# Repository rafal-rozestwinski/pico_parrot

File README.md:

# pico_parrot

Baofeng Parrot Simplex Repeater by Rafał Rozestwiński, https://github.com/rafal-rozestwinski/pico_parrot

- Listens for transmission,
- If audio level is high, it records audio for 10s,
- After 10s, triggers PTT on baofeng,
- plays beep (from sample.h),
- plays recorded audio,
- plays beep, releases PTT.

Based on https://github.com/rgrosset/pico-pwm-audio

Refer to it on how to generate own sample.h header with a custom beep (you may want to put your callsign there).

## Board

## Schematic

[schematic.pdf](/schematic.pdf)

## BoM

Footprints are duplicated - either SMT or THT parts can be used.
All part values are written on the PCB itself.

- 1x Raspberry Pi Pico
- 1x BJT transistor 2n3904
- 2x PCB Audio Jack Socket PJ-307
- 2x 100nF capacitor
- 1x bigger capacitor (10uF+)
- Resitors:
  - 2x 1000R pot, tht, RM-065_Vertical
  - 220
  - 100
  - 2x 1.8k
  - 2x 68k (or 56k... or 92k etc.) 

Optional power supply regulator pads are for AMS1117-5.0V.

## Future Plans

- Detect end of transmission and play back sooner.
- Easy way to change beep: littlefs has been added, need to add USB Mass Storage support, so those can be replaced without recompiling the code.
- Remote control over USB?
- 3D printed case

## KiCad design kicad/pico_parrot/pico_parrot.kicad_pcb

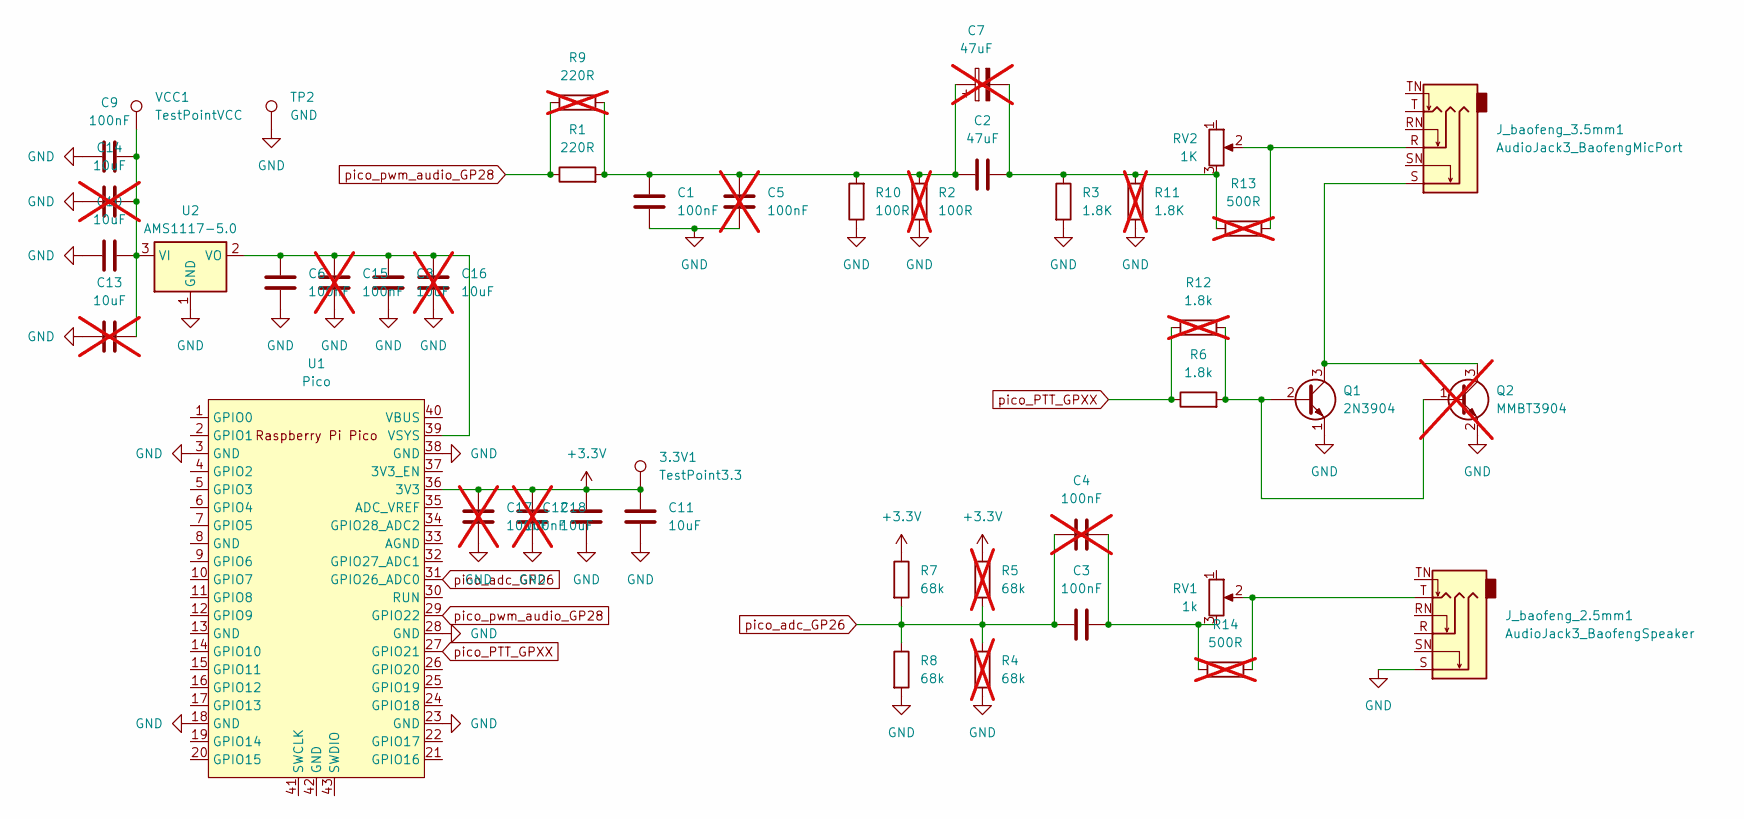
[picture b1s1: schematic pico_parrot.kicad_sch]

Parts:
3.3V1: TestPoint3.3; TestPoint_Pad_2.0x2.0mm
C1, C3, C6, C9, C12: 100nF; C_1206_3216Metric
C2: 47uF; C_1206_3216Metric
C4, C5, C15, C17: 100nF; C_Disc_D4.3mm_W1.9mm_P5.00mm; not fitted
C7: 47uF; CP_Radial_D5.0mm_P2.50mm; not fitted
C8, C10, C11: 10uF; C_1206_3216Metric
C13, C14, C16, C18: 10uF; C_Disc_D4.3mm_W1.9mm_P5.00mm; not fitted
J_baofeng_2.5mm1: AudioJack3_BaofengSpeaker; PJ-307_Modded
J_baofeng_3.5mm1: AudioJack3_BaofengMicPort; PJ-307_Modded
Q1: 2N3904; TO-92_Inline
Q2: MMBT3904; SOT-23; not fitted
R1: 220R; R_1206_3216Metric
R2: 100R; R_Axial_DIN0207_L6.3mm_D2.5mm_P2.54mm_Vertical; not fitted
R3: 1.8K; R_1206_3216Metric
R4, R5: 68k; R_Axial_DIN0207_L6.3mm_D2.5mm_P2.54mm_Vertical; not fitted
R6: 1.8k; R_1206_3216Metric
R7, R8: 68k; R_1206_3216Metric
R9: 220R; R_Axial_DIN0207_L6.3mm_D2.5mm_P2.54mm_Vertical; not fitted
R10: 100R; R_1206_3216Metric
R11: 1.8K; R_Axial_DIN0207_L6.3mm_D2.5mm_P2.54mm_Vertical; not fitted
R12: 1.8k; R_Axial_DIN0207_L6.3mm_D2.5mm_P2.54mm_Vertical; not fitted
R13, R14: 500R; R_1206_3216Metric; not fitted
RV1: 1k; Potentiometer_Runtron_RM-065_Vertical
RV2: 1K; Potentiometer_Runtron_RM-065_Vertical
TP2: GND; TestPoint_Pad_2.0x2.0mm
U1: Pico; RPi_Pico_SMD_TH
U2: AMS1117-5.0; SOT-223-3_TabPin2
VCC1: TestPointVCC; TestPoint_Pad_2.0x2.0mm

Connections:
+3.3V: 3.3V1.1, C11.2, C12.2, C17.1, C18.1, R5.1, R7.1, U1.36 (3V3)
GND: C1.1, C5.1, C6.1, C8.1, C9.2, C10.2, C11.1, C12.1, C13.2, C14.2, C15.2, C16.2, C17.2, C18.2, J_baofeng_2.5mm1.S, Q1.1 (E), Q2.2 (E), R2.1, R3.2, R4.2, R8.2, R10.1, R11.2, TP2.1, U1.3 (GND), U1.18 (GND), U1.23 (GND), U1.28 (GND), U1.38 (GND), U2.1 (GND)
unnamed: C1.2, C2.1, C5.2, C7.1, R1.2, R2.2, R9.2, R10.2
unnamed: C2.2, C7.2, R3.1, R11.1, R13.1, RV2.3
unnamed: C3.2, C4.2, R14.1, RV1.3
unnamed: J_baofeng_2.5mm1.T, R14.2, RV1.2
unnamed: J_baofeng_3.5mm1.R, R13.2, RV2.2
unnamed: Q1.2 (B), Q2.1 (B), R6.2, R12.2
unnamed: J_baofeng_3.5mm1.S, Q1.3 (C), Q2.3 (C)
unnamed: C6.2, C8.2, C15.1, C16.1, U1.39 (VSYS), U2.2 (VO)
unnamed: C9.1, C10.1, C13.1, C14.1, U2.3 (VI), VCC1.1
pico_PTT_GPXX: R6.1, R12.1, U1.27 (GPIO21)
pico_adc_GP26: C3.1, C4.1, R4.1, R5.2, R7.2, R8.1, U1.31 (GPIO26_ADC0)
pico_pwm_audio_GP28: R1.1, R9.1, U1.29 (GPIO22)

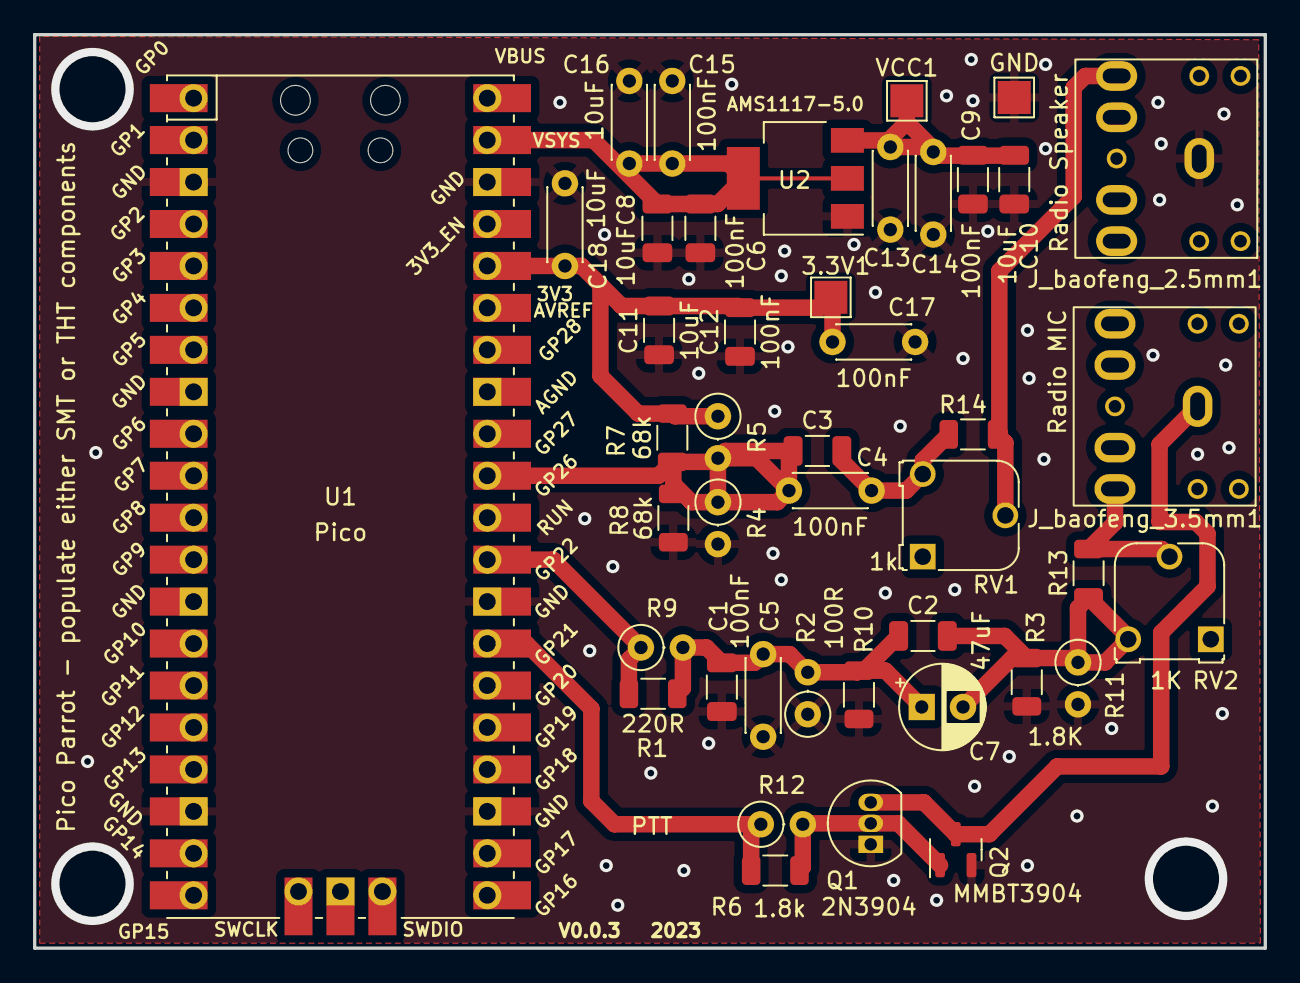
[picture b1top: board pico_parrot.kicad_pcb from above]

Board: 2 copper layers, 74.5 x 55.3 mm, 43 parts (0 on the bottom side), 14 nets.

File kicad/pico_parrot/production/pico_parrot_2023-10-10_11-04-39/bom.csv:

Designator,Footprint,Quantity,Value,LCSC Part #
3.3V,TestPoint_Pad_2.0x2.0mm,1,TestPoint3.3,
"C1, C12, C3, C6, C9",1206,5,100nF,
"C10, C11, C8",1206,3,10uF,
"C13, C14, C16, C18",C_Disc_D4.3mm_W1.9mm_P5.00mm,4,10uF,DNP
"C15, C17, C4, C5",C_Disc_D4.3mm_W1.9mm_P5.00mm,4,100nF,DNP
C2,1206,1,47uF,
C7,CP_Radial_D5.0mm_P2.50mm,1,47uF,DNP
J_baofeng_2.5mm,PJ-307_Modded,1,AudioJack3_BaofengSpeaker,
J_baofeng_3.5mm,PJ-307_Modded,1,AudioJack3_BaofengMicPort,
Q1,TO-92_Inline,1,2N3904,
Q2,SOT-23,1,MMBT3904,DNP
R1,1206,1,220R,
R10,1206,1,100R,
"R11, R12",R_Axial_DIN0207_L6.3mm_D2.5mm_P2.54mm_Vertical,2,1.8K,DNP
"R13, R14",1206,2,500R,DNP
R2,R_Axial_DIN0207_L6.3mm_D2.5mm_P2.54mm_Vertical,1,100R,DNP
"R3, R6",1206,2,1.8K,
"R4, R5",R_Axial_DIN0207_L6.3mm_D2.5mm_P2.54mm_Vertical,2,68k,DNP
"R7, R8",1206,2,68k,
R9,R_Axial_DIN0207_L6.3mm_D2.5mm_P2.54mm_Vertical,1,220R,DNP
"RV1, RV2",Potentiometer_Runtron_RM-065_Vertical,2,1k,
TP2,TestPoint_Pad_2.0x2.0mm,1,GND,
U1,RPi_Pico_SMD_TH,1,Pico,
U2,SOT-223-3_TabPin2,1,AMS1117-5.0,
VCC,TestPoint_Pad_2.0x2.0mm,1,TestPointVCC,

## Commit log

2023-10-09 initial
2023-10-09 itworks
2023-10-10 parrot
2023-11-07 license
2023-11-07 boards
2023-11-07 todo
2024-02-08 remove filesystem for now
2025-05-24 irq-adc+autostop
